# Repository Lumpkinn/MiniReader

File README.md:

<h1>Overview</h1>
This project is a small TFT using a Raspberry Pi Pico 2 to take text from a SD card and allow the user go through the text.

<h2>Additional Information</h2>
The code for the project is written in circuit python, and has been commented out to help users modify it.
The .gerber files are also included as well.
(here are some photos of the PCB)

<h3>BOM</h3>

| Item        | Amount | Unit Price  | Total | Vendor |
| :---------: |:------:| :----------:|:-----:|:------:|
| MicroSD Breakout Board  | 1 | $7.50 |$7.50|<a href="https://www.adafruit.com/product/254">Adafruit</a>|
| Adafruit 1.44 TFT Display |1|$14.95|$14.95|<a href="https://www.adafruit.com/product/2088">Adafruit</a>|
| Potentiometer|1|$1.25|$1.25|<a href="https://www.adafruit.com/product/4133">Adafruit</a>|
|Raspberry Pi Pico 2|1|$5.00|$5.00|<a href="https://www.pishop.us/product/raspberry-pi-pico-2/?src=raspberrypi">PiShop</a>|
|Connectors|1|$0.86|$0.86|<a href="https://www.peconnectors.com/cart">PeConnectors</a>|
|PCB|1|$4.00|$4.00|<a href="https://www.jlcpcb.com/">jlcpcb</a>|

Total = 33.56

<h4>Attributions</h4>
No AI was used for this project.

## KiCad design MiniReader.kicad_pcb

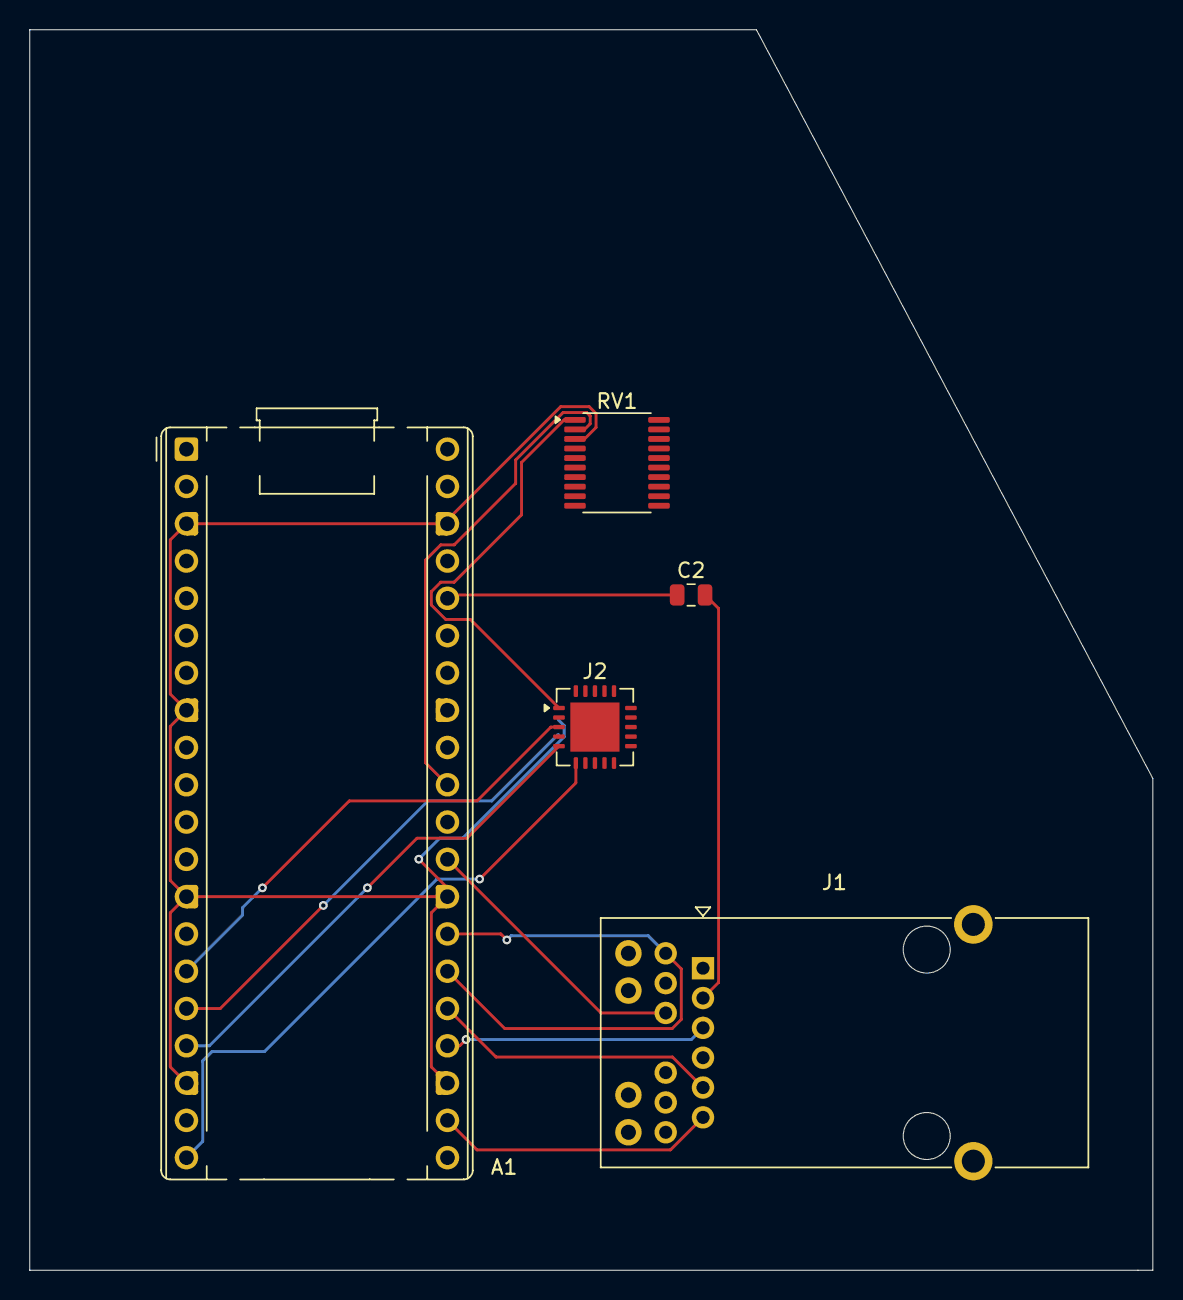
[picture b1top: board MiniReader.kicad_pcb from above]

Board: 2 copper layers, 76.5 x 84.5 mm, 5 parts (0 on the bottom side), 14 nets.

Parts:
A1: RaspberryPi_Pico; RaspberryPi_Pico_Common_THT
C2: 10 µF; C_0805_2012Metric
J1: Conn_01x09; RJ45_Pulse_JK0654219NL_Horizontal
J2: Conn_01x06; QFN-20-1EP_5x5mm_P0.65mm_EP3.35x3.35mm
RV1: R_Potentiometer; TSSOP-20_4.4x6.5mm_P0.65mm

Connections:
+3.3V: A1.36 (3V3), C2.1
+3V3: J2.1, RV1.1
/ADC_IN: A1.31 (GPIO26_ADC0), RV1.2
/BL: A1.29 (GPIO22), J1.9
/CS: A1.22 (GPIO17), J1.6
/DC: A1.26 (GPIO20), J1.7
/GPIO11: A1.16 (GPIO12), J2.4
/GPIO12: A1.17 (GPIO13), J2.5
/GPIO13: A1.20 (GPIO15), J2.6
/GPIO15: A1.15 (GPIO11), J2.3
/MOSI: A1.25 (GPIO19), J1.5
/SCK: A1.24 (GPIO18), J1.3
GND: A1.3 (GND), A1.8 (GND), A1.13 (GND), A1.18 (GND), A1.23 (GND), A1.28 (GND), A1.38 (GND), J2.2, RV1.3
unnamed: C2.2, J1.2
